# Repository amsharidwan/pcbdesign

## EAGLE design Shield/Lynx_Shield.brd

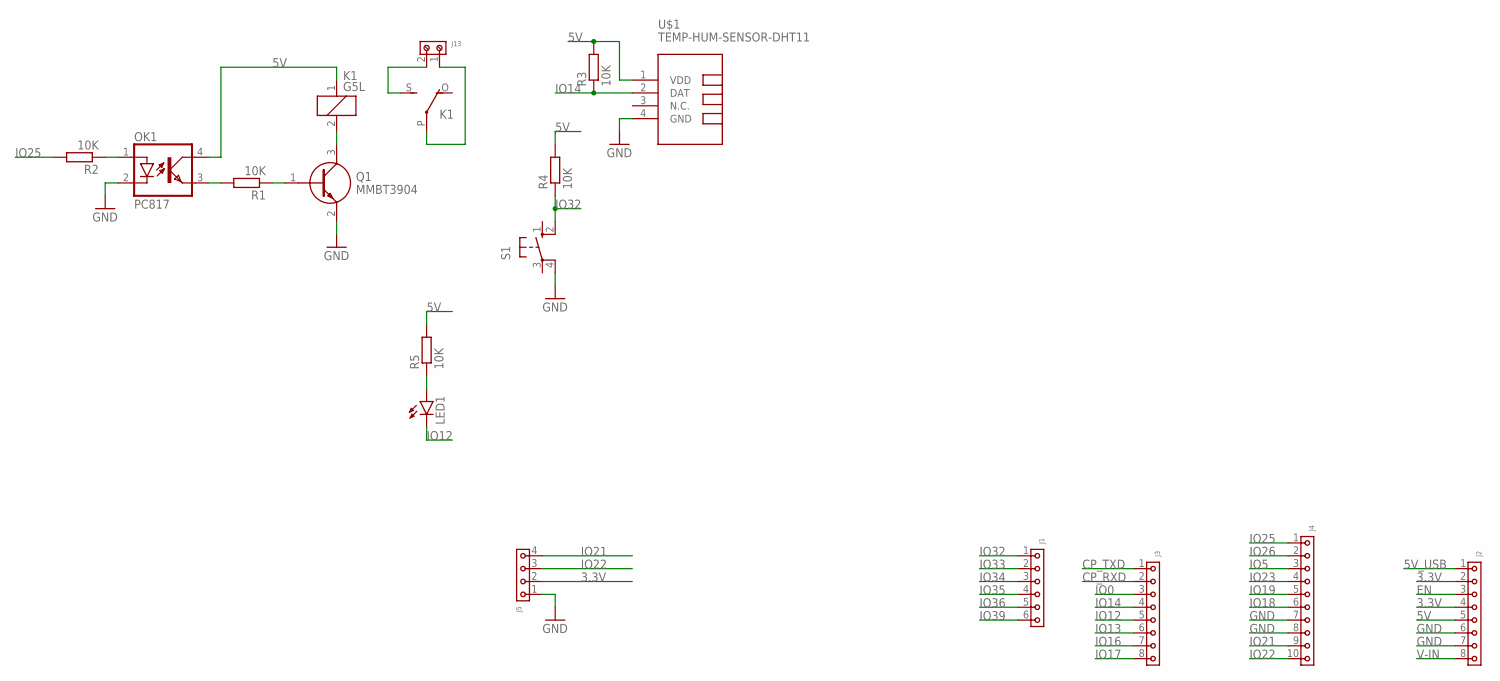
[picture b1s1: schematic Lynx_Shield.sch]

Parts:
J1: 6130XX11821_61300611821; 61300611821
J2, J3: 6130XX11821_61300811821; 61300811821
J4: 6130XX11821_61301011821; 61301011821
J5: 6130XX11821_61300411821; 61300411821
J13: 691134710002
K1: G5L; G5LE
LED1: LED5MM
OK1: PC817; DIL04
Q1: MMBT3904; SOT95P240X120-3N
R1, R2, R3, R4, R5: 10K; R0603
S1: 10-XX; B3F-10XX
U$1: TEMP-HUM-SENSOR-DHT11

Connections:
3.3V: J2.2, J2.4, J5.2
5V: J2.5, K1.1, OK1.4 (COL), R3.2, R4.2, R5.2, U$1.1 (VDD)
5V_USB: J2.1
CP_RXD: J3.2
CP_TXD: J3.1
EN: J2.3
GND: J2.6, J2.7, J4.7, J4.8, J5.1, OK1.2 (C), Q1.2 (E), S1.4 (P1), U$1.4 (GND)
IO0: J3.3
IO5: J4.3
IO12: J3.5, LED1.K (C)
IO13: J3.6
IO14: J3.4, R3.1, U$1.2 (DAT)
IO16: J3.7
IO17: J3.8
IO18: J4.6
IO19: J4.5
IO21: J4.9, J5.4
IO22: J4.10, J5.3
IO23: J4.4
IO25: J4.1, R2.2
IO26: J4.2
IO32: J1.1, R4.1, S1.2 (S1)
IO33: J1.2
IO34: J1.3
IO35: J1.4
IO36: J1.5
IO39: J1.6
unnamed: OK1.3 (EMIT), R1.2
unnamed: J13.2, K1.S
unnamed: J13.1, K1.P
unnamed: OK1.1 (A), R2.1
unnamed: K1.2, Q1.3 (C)
unnamed: Q1.1 (B), R1.1
unnamed: LED1.A, R5.1
V-IN: J2.8

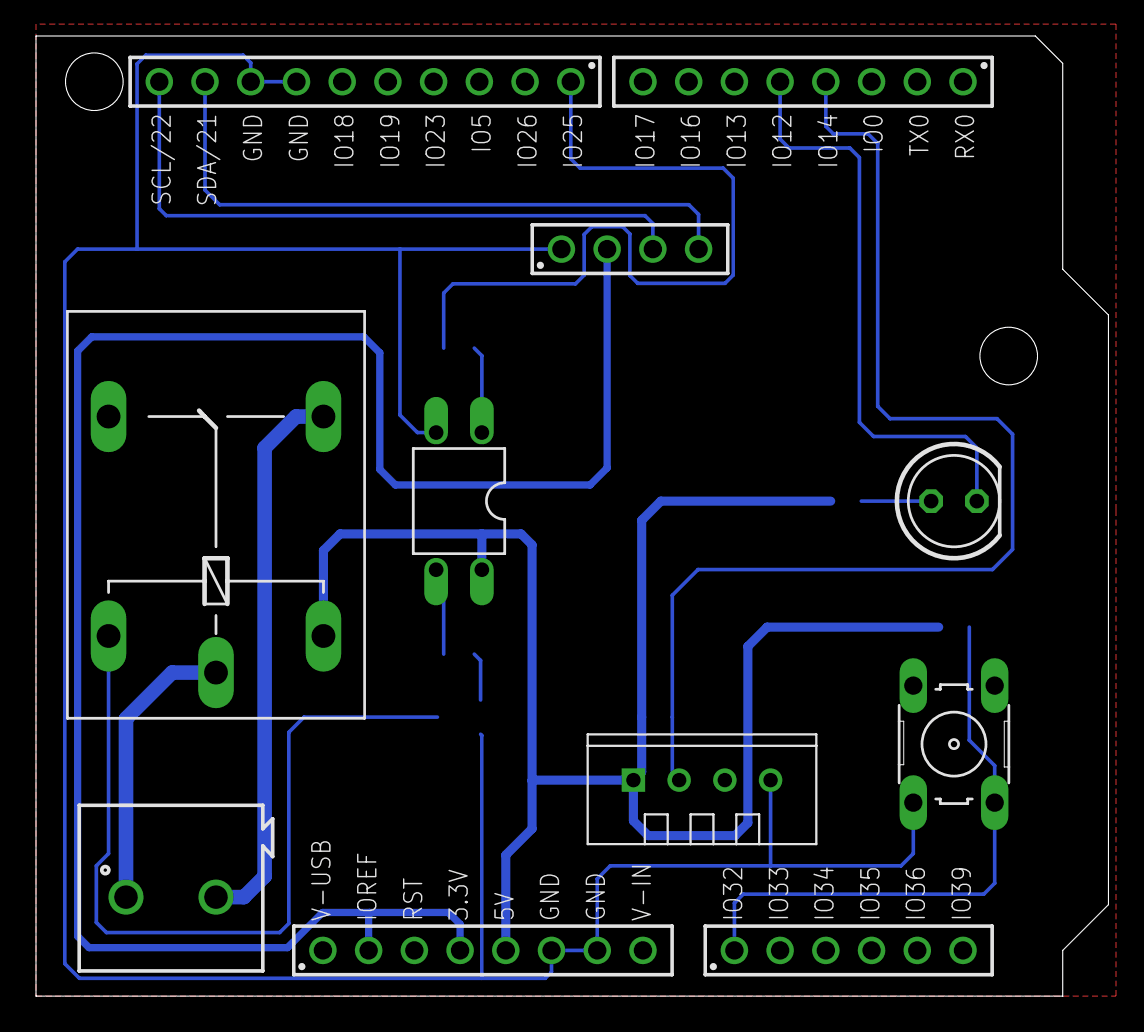
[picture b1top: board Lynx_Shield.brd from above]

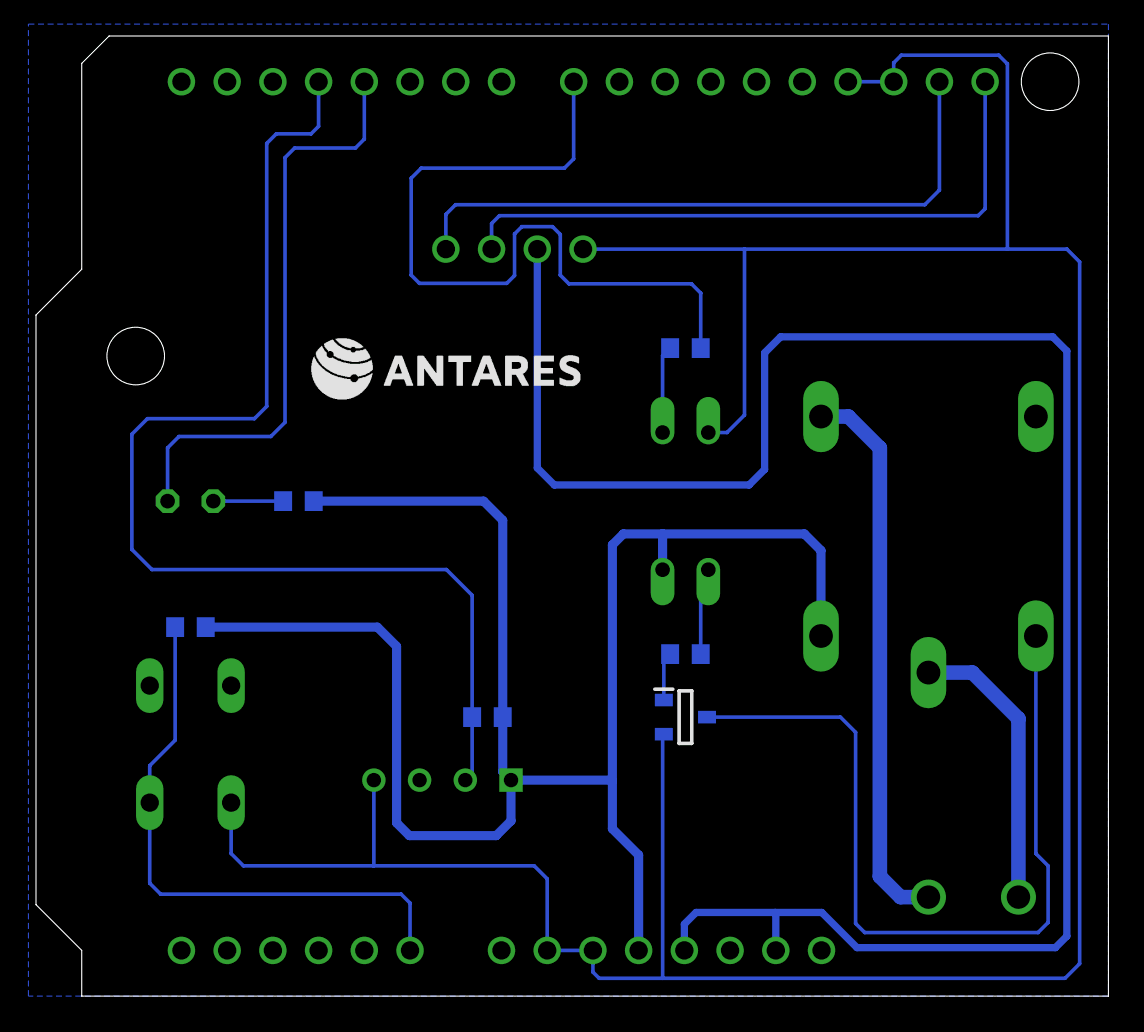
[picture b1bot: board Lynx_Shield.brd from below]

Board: 2 copper layers, 59.6 x 53.3 mm, 17 parts (6 on the bottom side), 16 nets.

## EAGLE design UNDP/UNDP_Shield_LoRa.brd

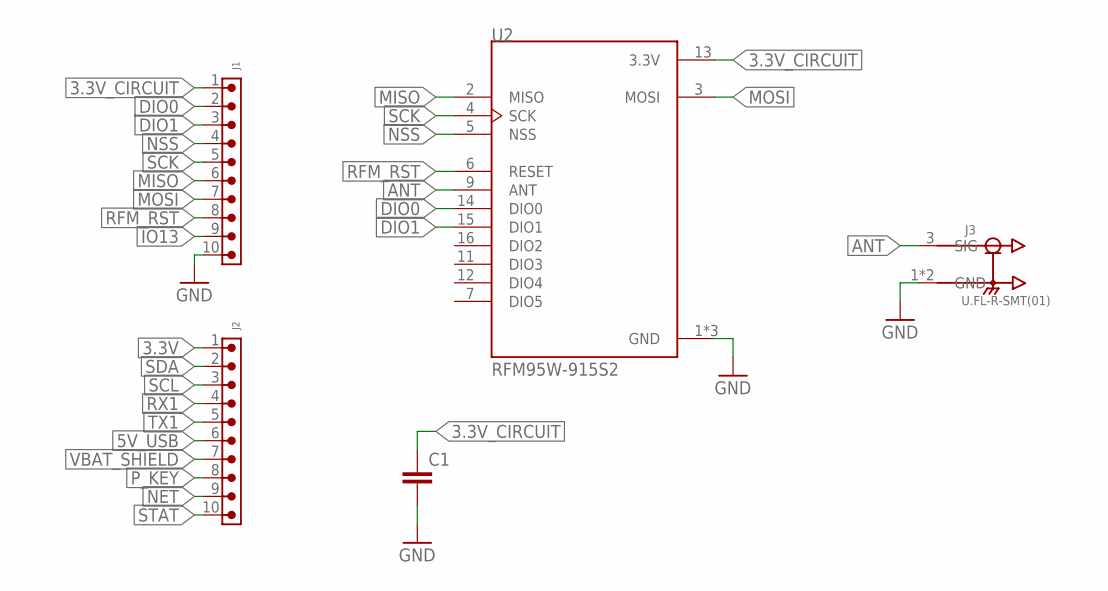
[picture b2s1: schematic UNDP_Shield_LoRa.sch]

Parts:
C1: C-EUC0603; C0603
J1, J2: 6200XX11121_62001011121; 62001011121
J3: U.FL-R-SMT(01); HRS_U.FL-R-SMT(01)
U2: RFM95W-915S2; XCVR_RFM95W-915S2

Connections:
3.3V: J2.1
3.3V_CIRCUIT: C1.1, J1.1, U2.13 (3.3V)
5V_USB: J2.6
ANT: J3.3 (SIG), U2.9 (ANT)
DIO0: J1.2, U2.14 (DIO0)
DIO1: J1.3, U2.15 (DIO1)
GND: C1.2, J1.10, J3.1 (GND), J3.2 (GND), U2.1 (GND), U2.8 (GND), U2.10 (GND)
IO13: J1.9
MISO: J1.6, U2.2 (MISO)
MOSI: J1.7, U2.3 (MOSI)
NET: J2.9
NSS: J1.4, U2.5 (NSS)
P_KEY: J2.8
RFM_RST: J1.8, U2.6 (RESET)
RX1: J2.4
SCK: J1.5, U2.4 (SCK)
SCL: J2.3
SDA: J2.2
STAT: J2.10
TX1: J2.5
VBAT_SHIELD: J2.7

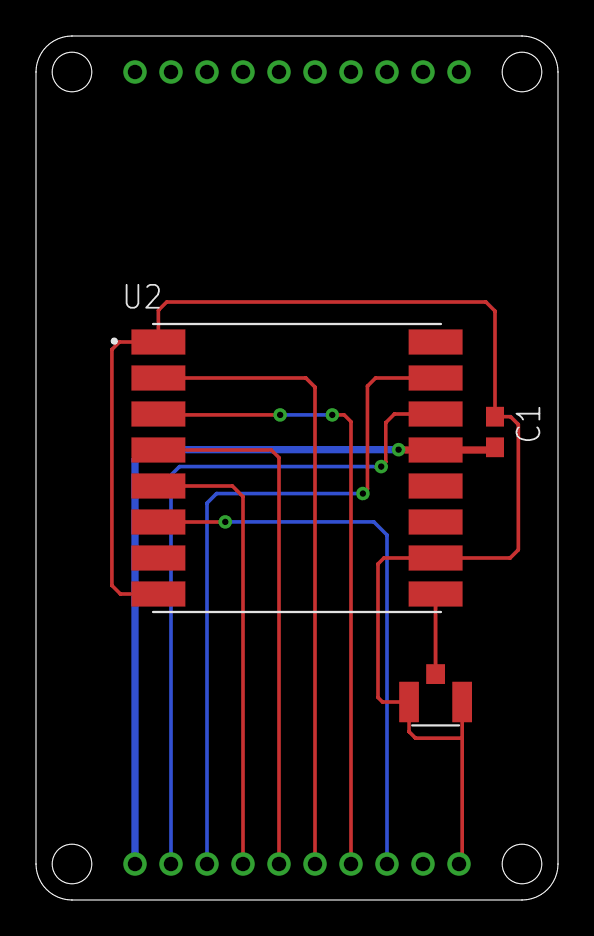
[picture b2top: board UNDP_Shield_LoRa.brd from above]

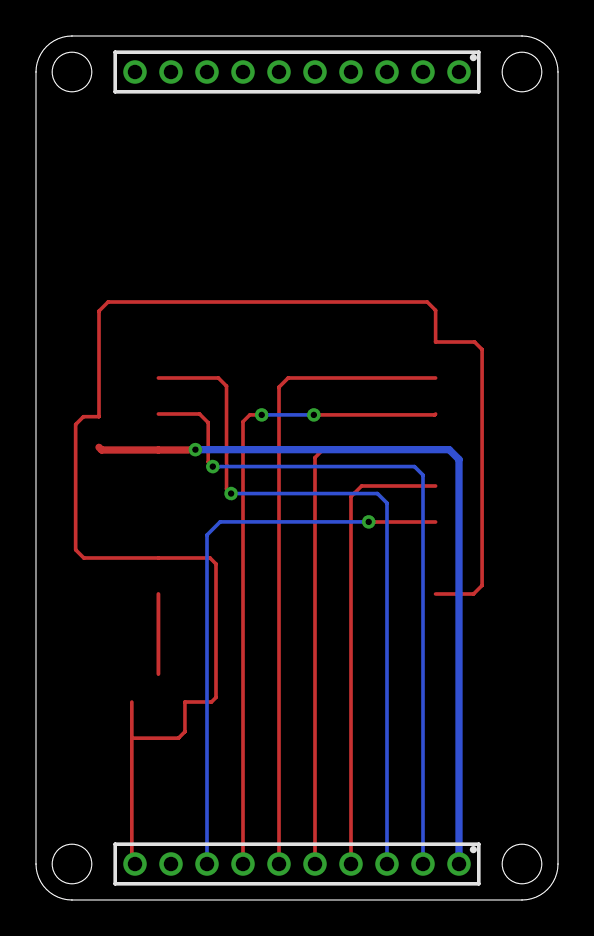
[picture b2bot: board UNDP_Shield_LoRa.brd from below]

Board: 2 copper layers, 29.0 x 48.0 mm, 5 parts (2 on the bottom side), 10 nets.

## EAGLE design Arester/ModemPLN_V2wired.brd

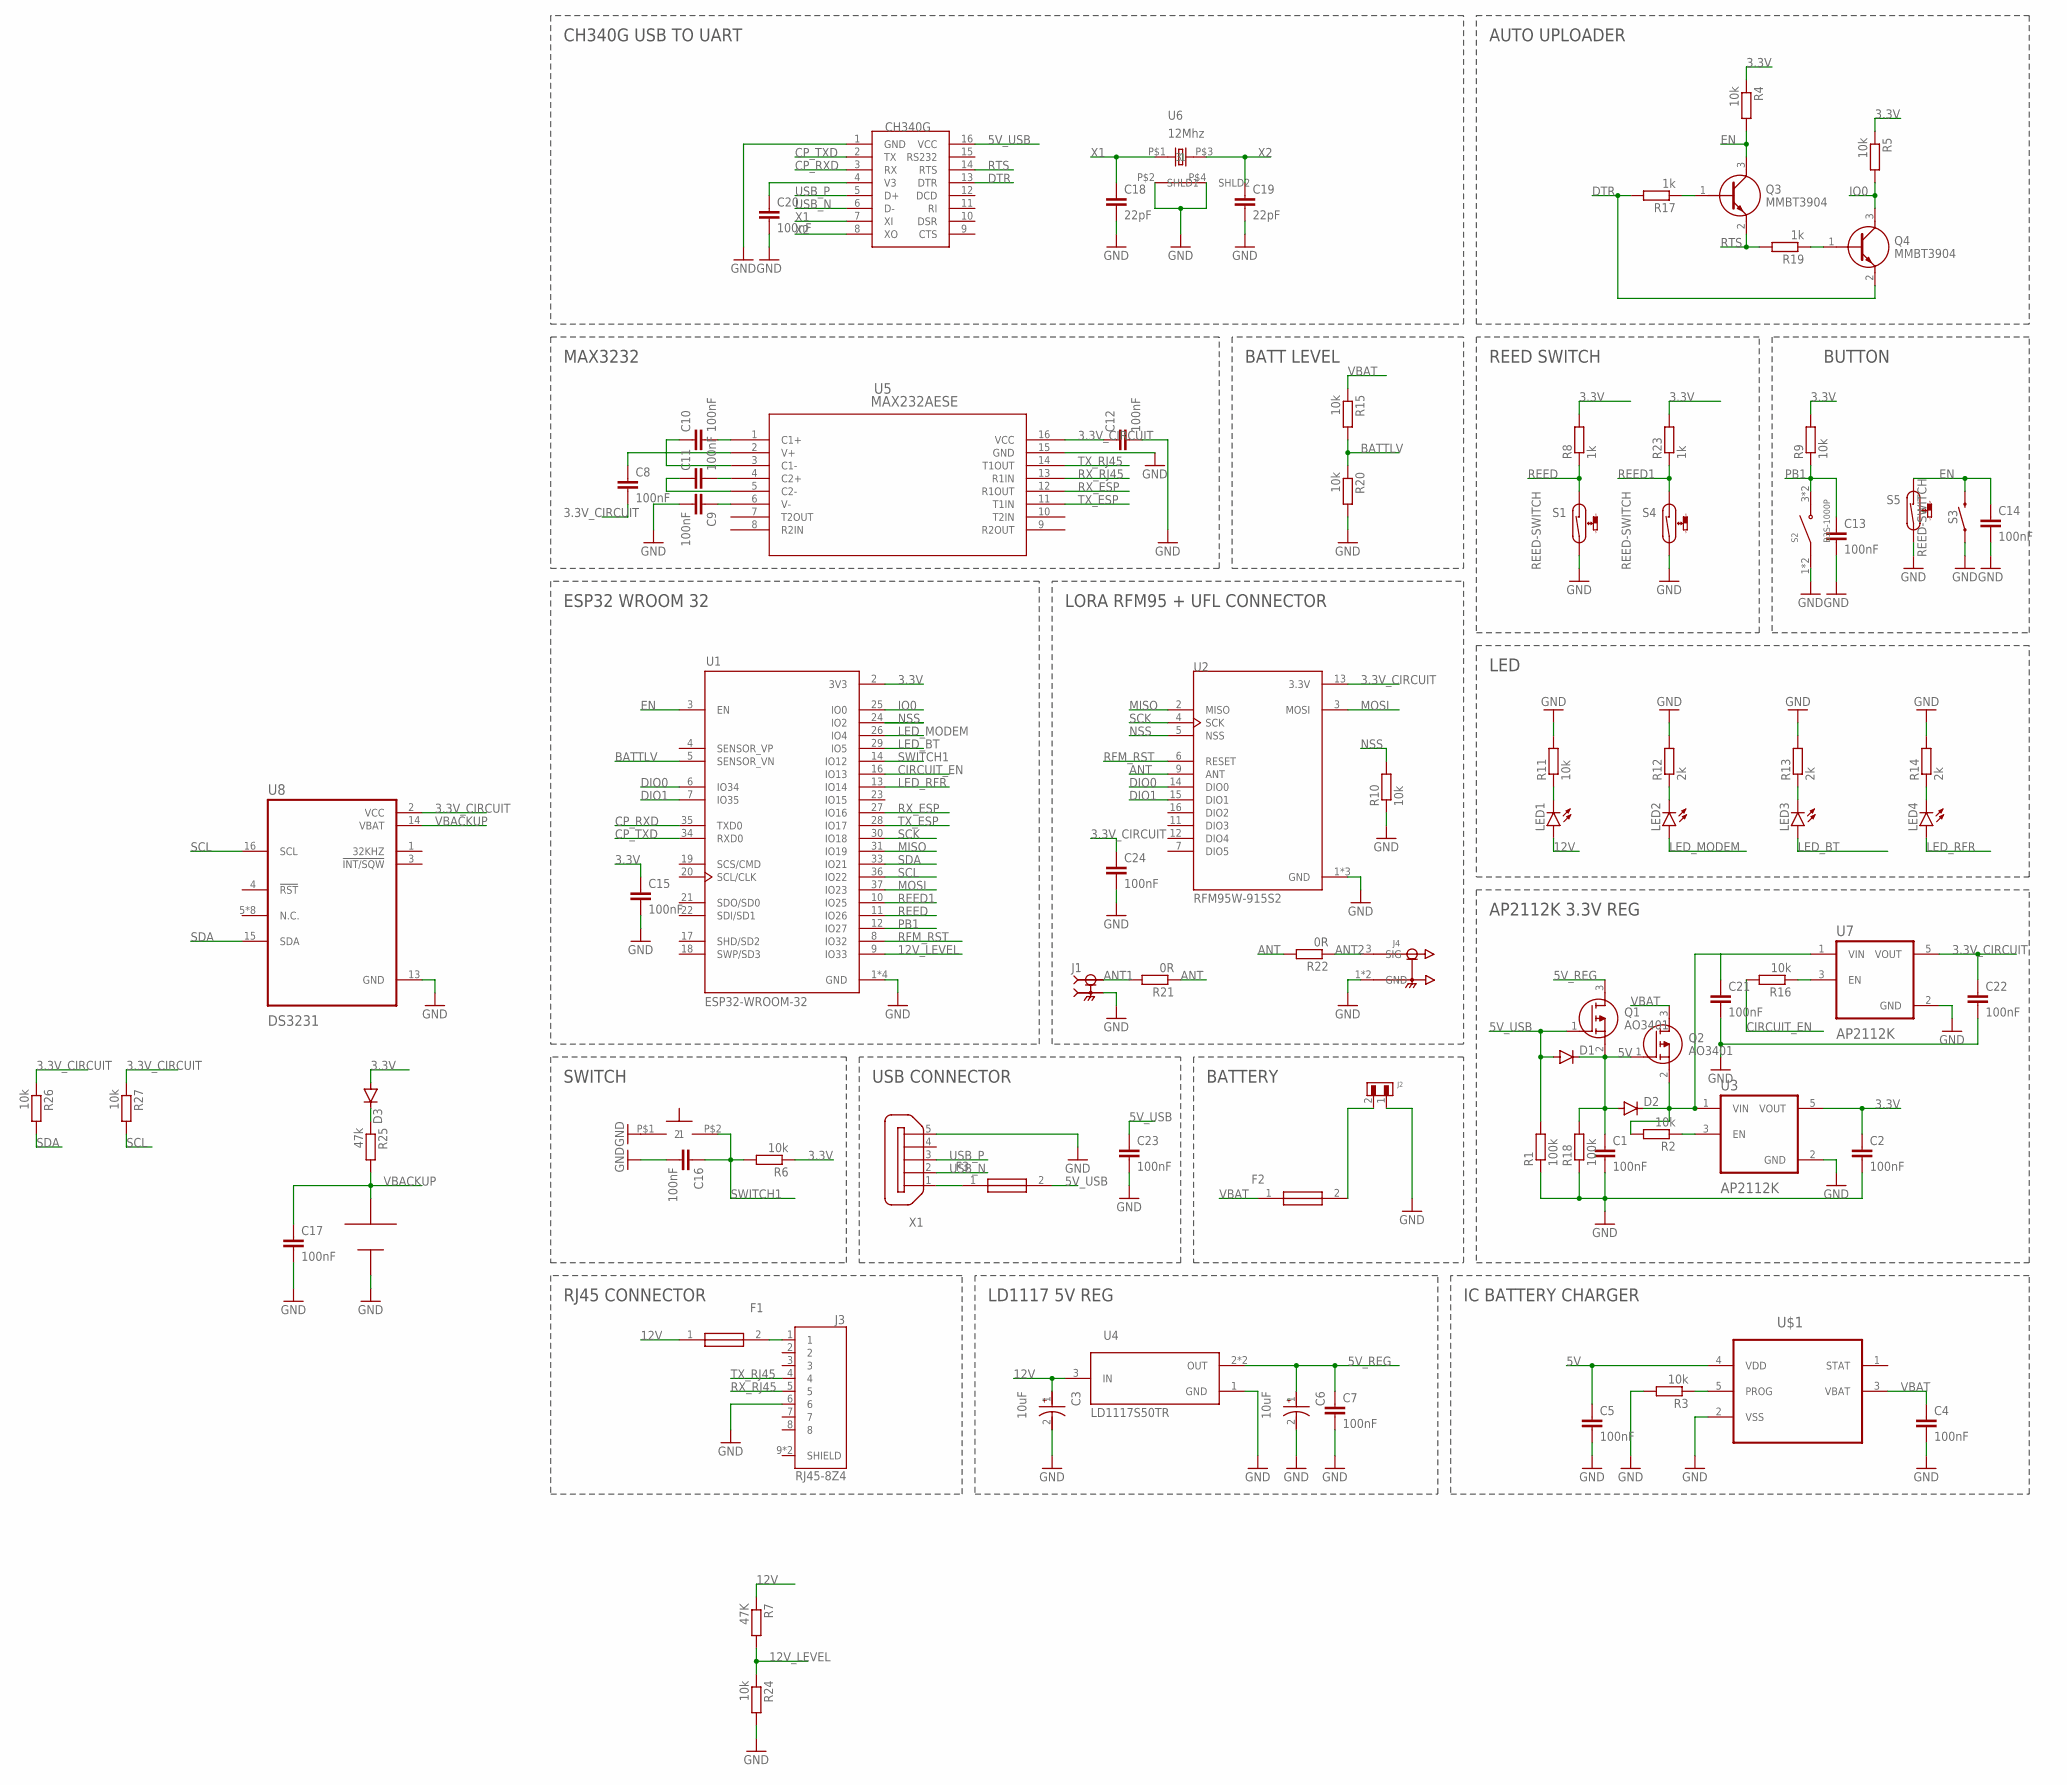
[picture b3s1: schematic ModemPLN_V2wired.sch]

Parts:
C1, C2, C4, C5, C7, C8, C9, C10, C11, C12, C13, C14, C15, C16, C17, C20, C21, C22, C23, C24: 100nF; C0603
C3, C6: 10uF; CAPPM3528X210N
C18, C19: 22pF; C0603
D1, D2, D3: DIODE-DO214AC; DO214AC
F1, F2, F3: MF-NSML260_12-2; FUSC3216X100N
J1: SMA-J-P-X-RA-TH1; SAMTEC_SMA-J-P-X-RA-TH1
J2: 620102131822
J3: RJ45-8Z4; TE_RJ45-8Z4
J4: U.FL-R-SMT(01); HRS_U.FL-R-SMT(01)
LED1, LED2, LED3, LED4: LEDCHIPLED_0805; CHIPLED_0805
Q1, Q2: AO3401; SOT95P280X125-3N
Q3, Q4: MMBT3904; SOT95P240X120-3N
R1, R18: 100k; R0603
R2, R3, R4, R5, R6, R9, R10, R11, R15, R16, R20, R24, R26, R27: 10k; R0603
R7: 47K; R0603
R8, R17, R19, R23: 1k; R0603
R12, R13, R14: 2k; R0603
R21, R22: 0R; R0603
R25: 47k; R0603
S1, S4, S5: REED-SWITCH; MK15
S2: B3S-1000P; SW_B3S-1000P
S3: MOMENTARY-SWITCH-SPST-SMD-6.0X3.5MM; TACTILE_SWITCH_SMD_6.0X3.5MM
U1: ESP32-WROOM-32; MODULE_ESP32-WROOM-32(8MB)
U2: RFM95W-915S2; XCVR_RFM95W-915S2
U3, U7: AP2112K; SOT95P285X140-5N
U4: LD1117S50TR; SOT230P700X180-4N
U5: MAX232AESE; 21-0041B_16
U6: 12Mhz; NX32256A
U8: DS3231; SOIC127P1032X265-16N
U$1: MCP73831T-5ACI/OT; SOT95P280X145-5N
U$2: TACTSWITCH; TACT
U$3: MS621FE
U$4: CH340G; SOIC127P600X175-16N
X1: ZX62D-B-5PA8

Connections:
3.3V: C2.1, C15.1, D3.A, R4.1, R5.1, R6.1, R8.2, R9.2, R23.2, U1.2 (3V3), U3.5 (VOUT)
3.3V_CIRCUIT: C8.2, C12.1, C22.1, C24.1, R26.1, R27.1, U2.13 (3.3V), U5.16 (VCC), U7.5 (VOUT), U8.2 (VCC)
5V: C1.1, C5.1, D1.C, D2.A, Q1.2 (S), Q2.1 (G), R18.2, U$1.4 (VDD)
5V_REG: C6.1, C7.1, Q1.3 (D), U4.2 (OUT), U4.4 (OUT)
5V_USB: C23.1, D1.A, F3.2, Q1.1 (G), R1.2, U$4.16 (VCC)
12V: C3.1, F1.1, LED1.A, R7.1, U4.3 (IN)
12V_LEVEL: R7.2, R24.1, U1.9 (IO33)
ANT: R21.1, R22.2, U2.9 (ANT)
ANT1: J1.1, R21.2
ANT2: J4.3 (SIG), R22.1
BATTLV: R15.2, R20.1, U1.5 (SENSOR_VN)
CIRCUIT_EN: R16.2, U1.16 (IO13)
CP_RXD: U1.35 (TXD0), U$4.3 (RX)
CP_TXD: U1.34 (RXD0), U$4.2 (TX)
DIO0: U1.6 (IO34), U2.14 (DIO0)
DIO1: U1.7 (IO35), U2.15 (DIO1)
DTR: Q4.2 (E), R17.2, U$4.13 (DTR)
EN: C14.1, Q3.3 (C), R4.2, S3.2, S5.1, U1.3 (EN)
GND: C1.2, C2.2, C3.2, C4.2, C5.2, C6.2, C7.2, C9.2, C12.2, C13.2, C14.2, C15.2, C16.2, C17.2, C18.2, C19.2, C20.2, C21.2, C22.2, C23.2, C24.2, J1.2, J1.3 (2), J1.4 (2), J1.5 (2), J2.1, J3.6, J4.1 (GND), J4.2 (GND), R1.1, R3.2, R10.1, R11.2, R12.2, R13.2, R14.2, R18.1, R20.2, R24.2, S1.2, S2.1 (COM), S2.2 (COM), S3.1, S4.2, S5.2, U1.1 (GND), U1.15 (GND), U1.38 (GND), U1.39 (GND), U2.1 (GND), U2.8 (GND), U2.10 (GND), U3.2 (GND), U4.1 (GND), U5.15 (GND), U6.P$2 (SHLD1), U6.P$4 (SHLD2), U7.2 (GND), U8.13 (GND), U$1.2 (VSS), U$2.P$1 (1), U$3.V-, U$4.1 (GND), X1.5
IO0: Q4.3 (C), R5.2, U1.25 (IO0)
LED_BT: LED3.A, U1.29 (IO5)
LED_MODEM: LED2.A, U1.26 (IO4)
LED_RFR: LED4.A, U1.13 (IO14)
MISO: U1.31 (IO19), U2.2 (MISO)
MOSI: U1.37 (IO23), U2.3 (MOSI)
unnamed: LED1.C, R11.1
unnamed: F1.2, J3.1
unnamed: R16.1, U7.3 (EN)
unnamed: R2.1, U3.3 (EN)
unnamed: R3.1, U$1.5 (PROG)
unnamed: C9.1, U5.6 (V-)
unnamed: LED2.C, R12.1
unnamed: C11.2, U5.4 (C2+)
unnamed: C11.1, U5.5 (C2-)
unnamed: C10.2, U5.1 (C1+)
unnamed: C10.1, U5.3 (C1-)
unnamed: LED3.C, R13.1
unnamed: LED4.C, R14.1
unnamed: C21.1, D2.C, Q2.2 (S), R2.2, U3.1 (VIN), U7.1 (VIN)
unnamed: C20.1, U$4.4 (V3)
unnamed: C8.1, U5.2 (V+)
unnamed: F3.1, X1.1
unnamed: D3.C, R25.1
unnamed: Q3.1 (B), R17.1
unnamed: Q4.1 (B), R19.1
unnamed: F2.2, J2.2
NSS: R10.2, U1.24 (IO2), U2.5 (NSS)
PB1: C13.1, R9.1, S2.3 (NO), S2.4 (NO), U1.12 (IO27)
REED: R8.1, S1.1, U1.11 (IO26)
REED1: R23.1, S4.1, U1.10 (IO25)
RFM_RST: U1.8 (IO32), U2.6 (RESET)
RTS: Q3.2 (E), R19.2, U$4.14 (RTS)
RX_ESP: U1.27 (IO16), U5.12 (R1OUT)
RX_RJ45: J3.5, U5.13 (R1IN)
SCK: U1.30 (IO18), U2.4 (SCK)
SCL: R27.2, U1.36 (IO22), U8.16 (SCL)
SDA: R26.2, U1.33 (IO21), U8.15 (SDA)
SWITCH1: C16.1, R6.2, U1.14 (IO12), U$2.P$2 (2)
TX_ESP: U1.28 (IO17), U5.11 (T1IN)
TX_RJ45: J3.4, U5.14 (T1OUT)
USB_N: U$4.6 (D-), X1.2
USB_P: U$4.5 (D+), X1.3
VBACKUP: C17.1, R25.2, U8.14 (VBAT), U$3.V+
VBAT: C4.1, F2.1, Q2.3 (D), R15.1, U$1.3 (VBAT)
X1: C18.1, U6.P$1 (1), U$4.7 (XI)
X2: C19.1, U6.P$3 (3), U$4.8 (XO)

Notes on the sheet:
SWITCH
RJ45 CONNECTOR
LD1117 5V REG
IC BATTERY CHARGER
BATTERY
AP2112K 3.3V REG
LED
LORA RFM95 + UFL CONNECTOR
ESP32 WROOM 32
MAX3232
BATT LEVEL
REED SWITCH
BUTTON
USB CONNECTOR
CH340G USB TO UART
AUTO UPLOADER

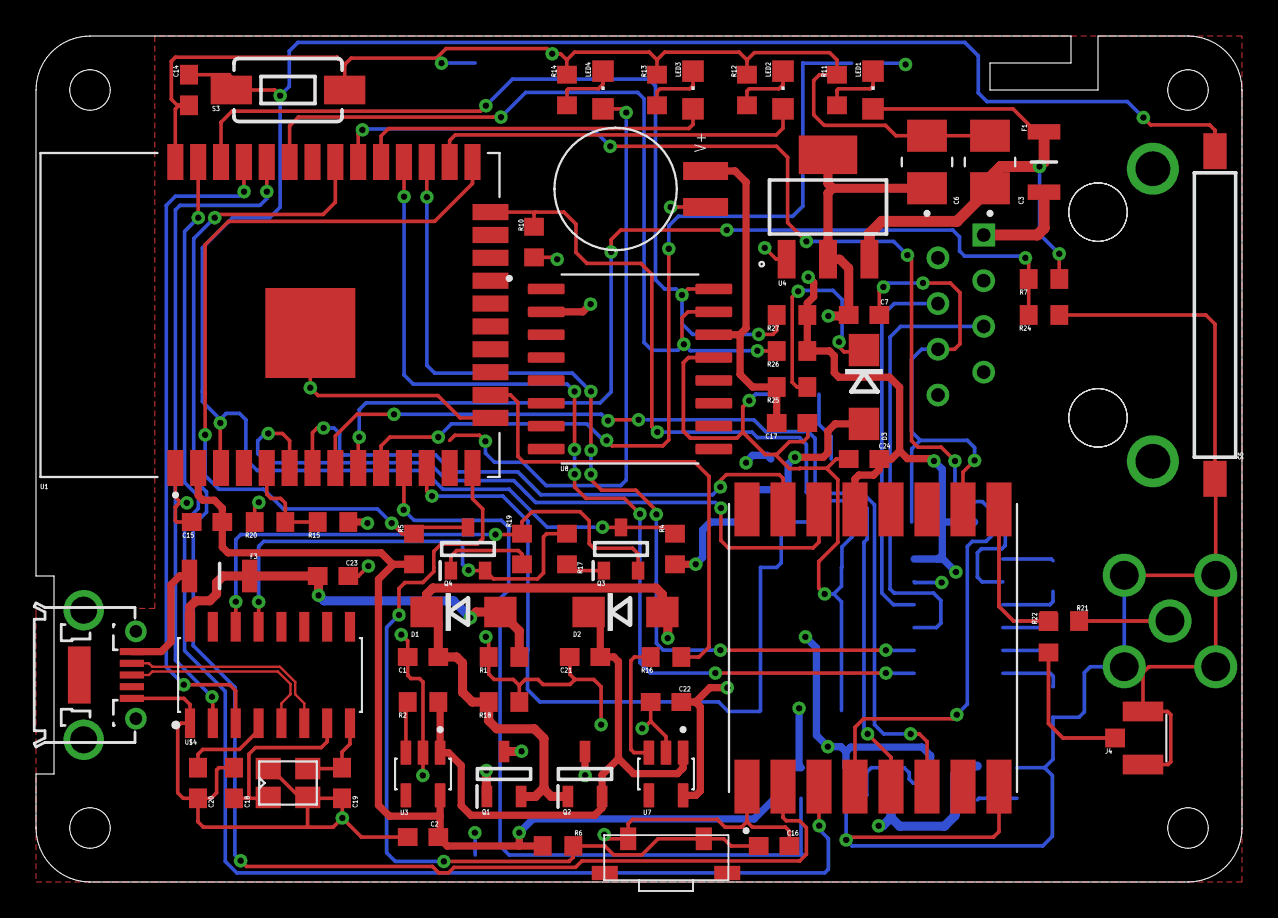
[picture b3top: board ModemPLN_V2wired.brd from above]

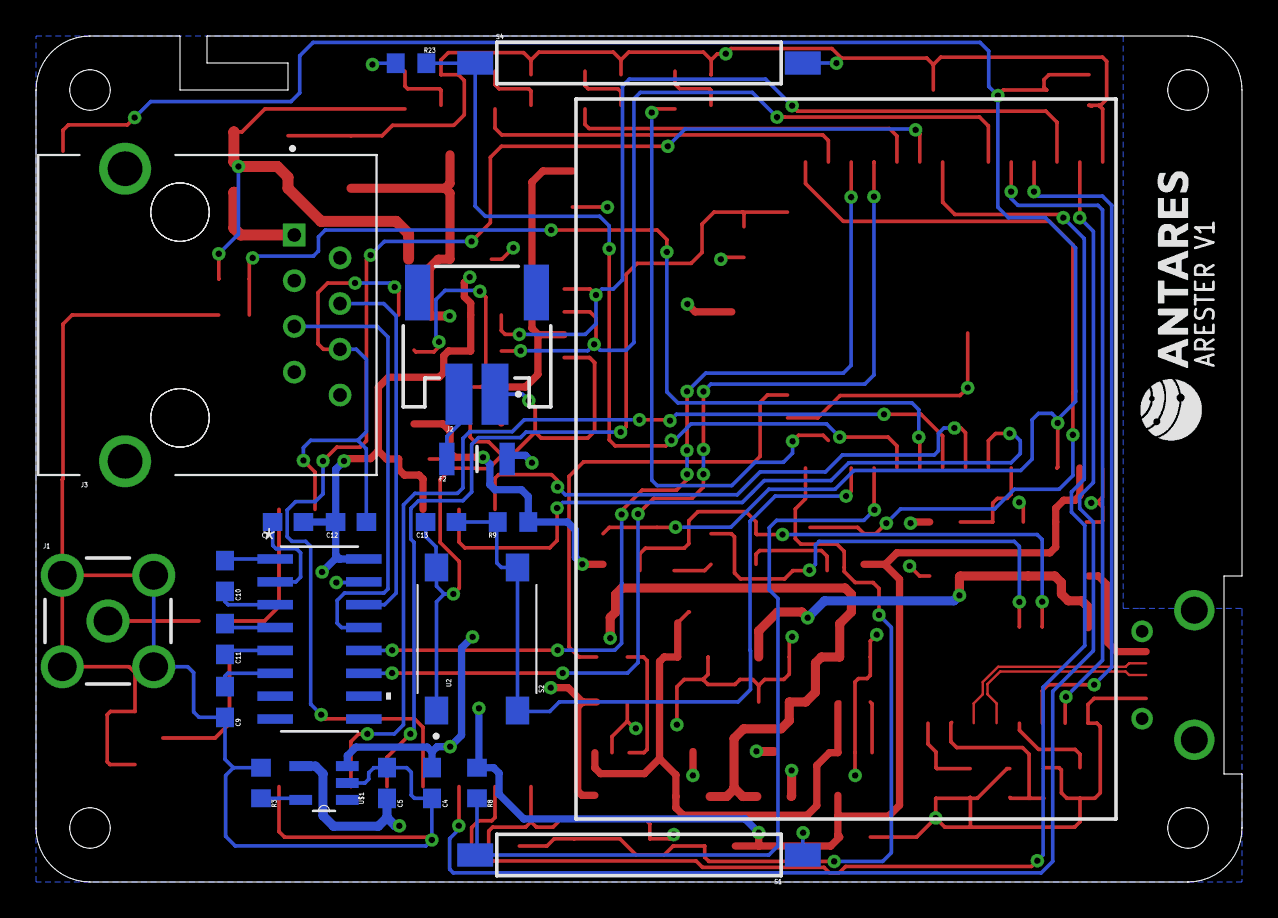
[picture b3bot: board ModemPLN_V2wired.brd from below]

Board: 4 copper layers, 67.0 x 47.0 mm, 87 parts (21 on the bottom side), 66 nets.

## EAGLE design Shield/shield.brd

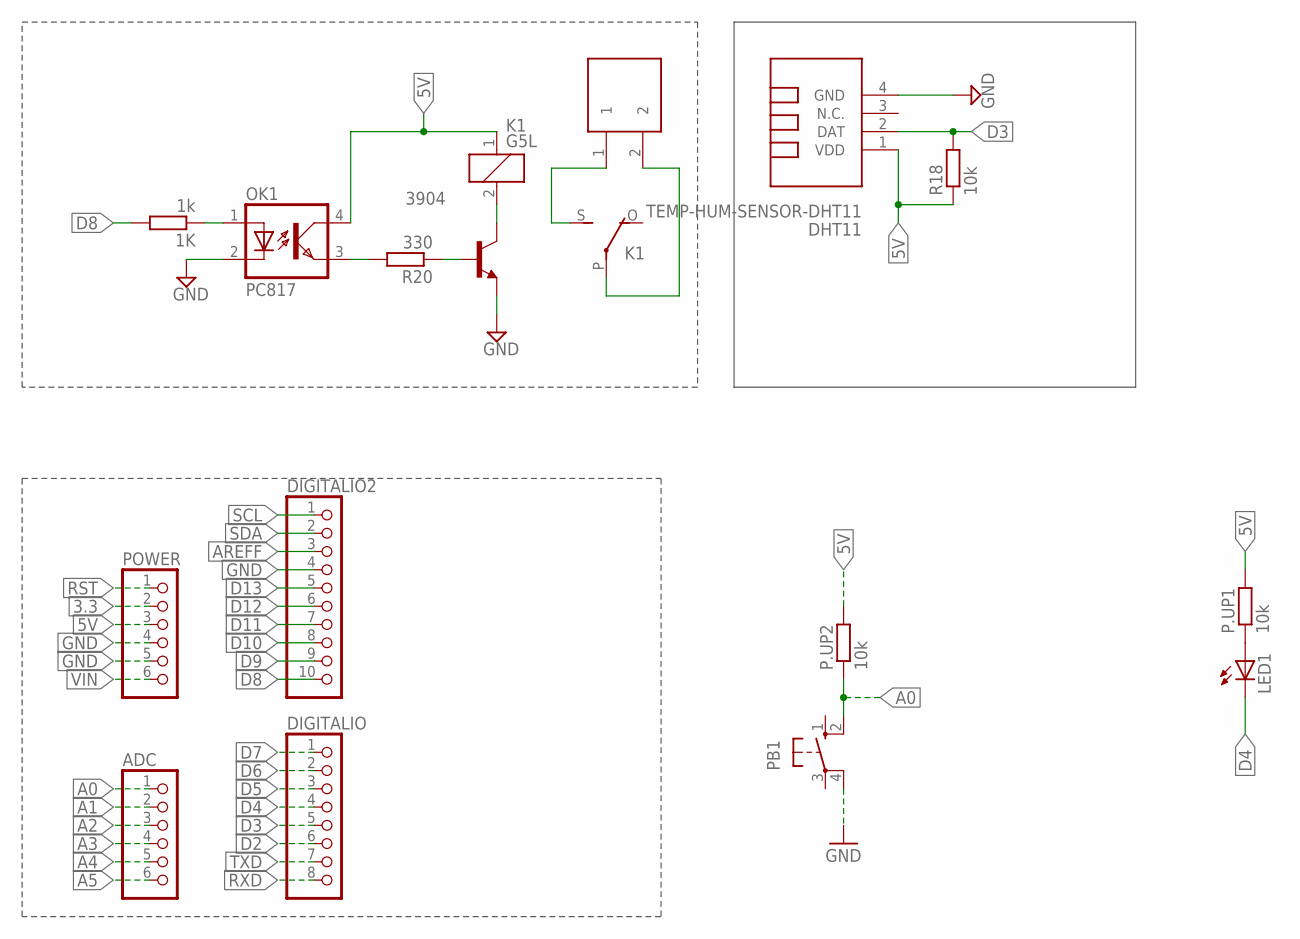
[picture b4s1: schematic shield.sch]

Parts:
1K: 1k; R0805
3904: MMBT3904LT1-NPN-SOT23-BEC; SOT23-BEC
ADC: PINHD-1X6; 1X06
DHT11: TEMP-HUM-SENSOR-DHT11
DIGITALIO: PINHD-1X8; 1X08
DIGITALIO2: PINHD-1X10; 1X10
K1: G5L; G5LE
LED1: LED5MM
OK1: PC817; DIL04
P.UP1, P.UP2: 10k; R0805
PB1: 10-XX; B3F-10XX
POWER: PINHD-1X6; 1X06
R18: 10k; R0805
R20: 330; R0805
U$8: TBLOCK2PIN; 2PIN

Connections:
3.3: POWER.2
5V: DHT11.1 (VDD), K1.1, OK1.4 (COL), P.UP1.2, P.UP2.2, POWER.3, R18.1
A0: ADC.1, P.UP2.1, PB1.2 (S1)
A1: ADC.2
A2: ADC.3
A3: ADC.4
A4: ADC.5
A5: ADC.6
AREFF: DIGITALIO2.3
D2: DIGITALIO.6
D3: DHT11.2 (DAT), DIGITALIO.5, R18.2
D4: DIGITALIO.4, LED1.K (C)
D5: DIGITALIO.3
D6: DIGITALIO.2
D7: DIGITALIO.1
D8: 1K.2, DIGITALIO2.10
D9: DIGITALIO2.9
D10: DIGITALIO2.8
D11: DIGITALIO2.7
D12: DIGITALIO2.6
D13: DIGITALIO2.5
GND: 3904.E, DHT11.4 (GND), DIGITALIO2.4, OK1.2 (C), PB1.4 (P1), POWER.4, POWER.5
LOAD: K1.P, U$8.2
unnamed: K1.S, U$8.1
unnamed: LED1.A, P.UP1.1
unnamed: 1K.1, OK1.1 (A)
unnamed: OK1.3 (EMIT), R20.2
unnamed: 3904.B, R20.1
unnamed: 3904.C, K1.2
RST: POWER.1
RXD: DIGITALIO.8
SCL: DIGITALIO2.1
SDA: DIGITALIO2.2
TXD: DIGITALIO.7
VIN: POWER.6

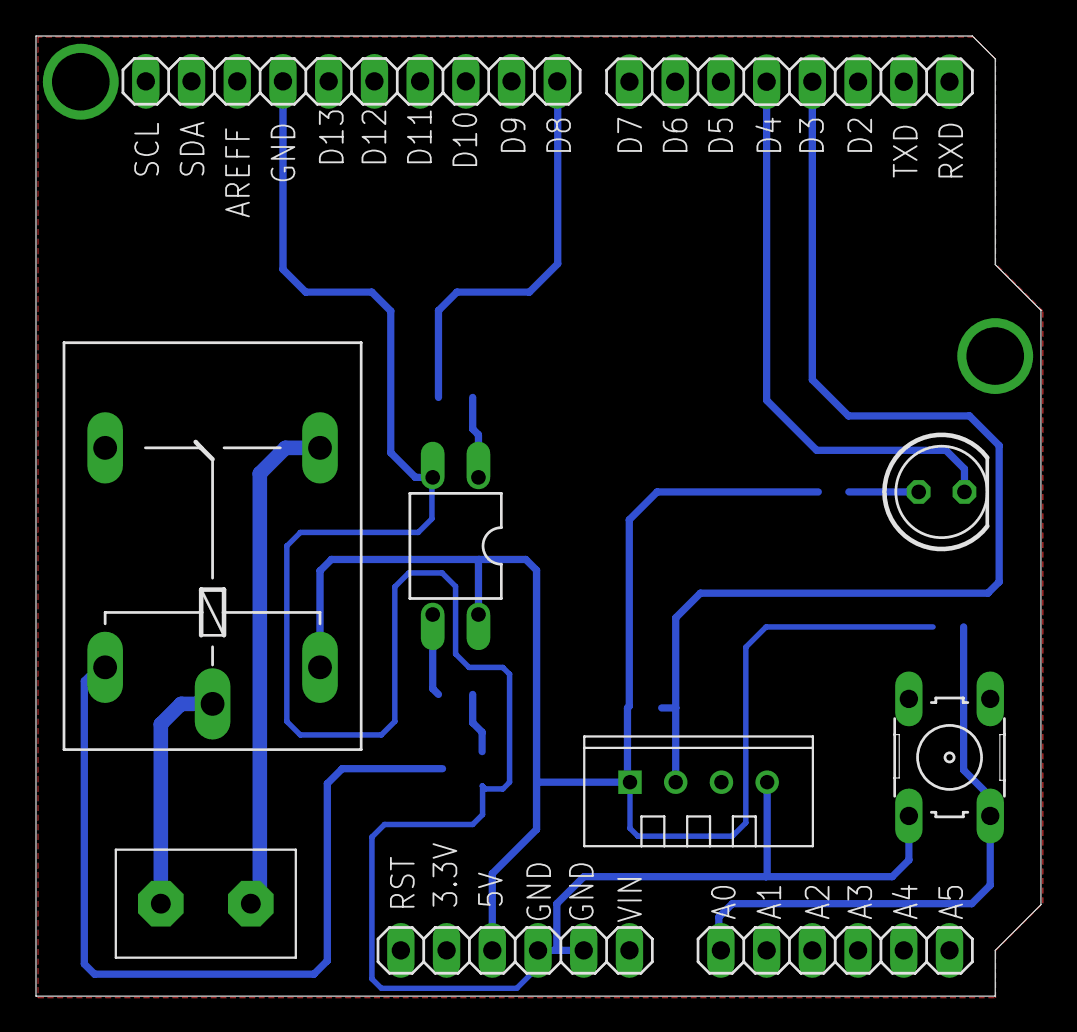
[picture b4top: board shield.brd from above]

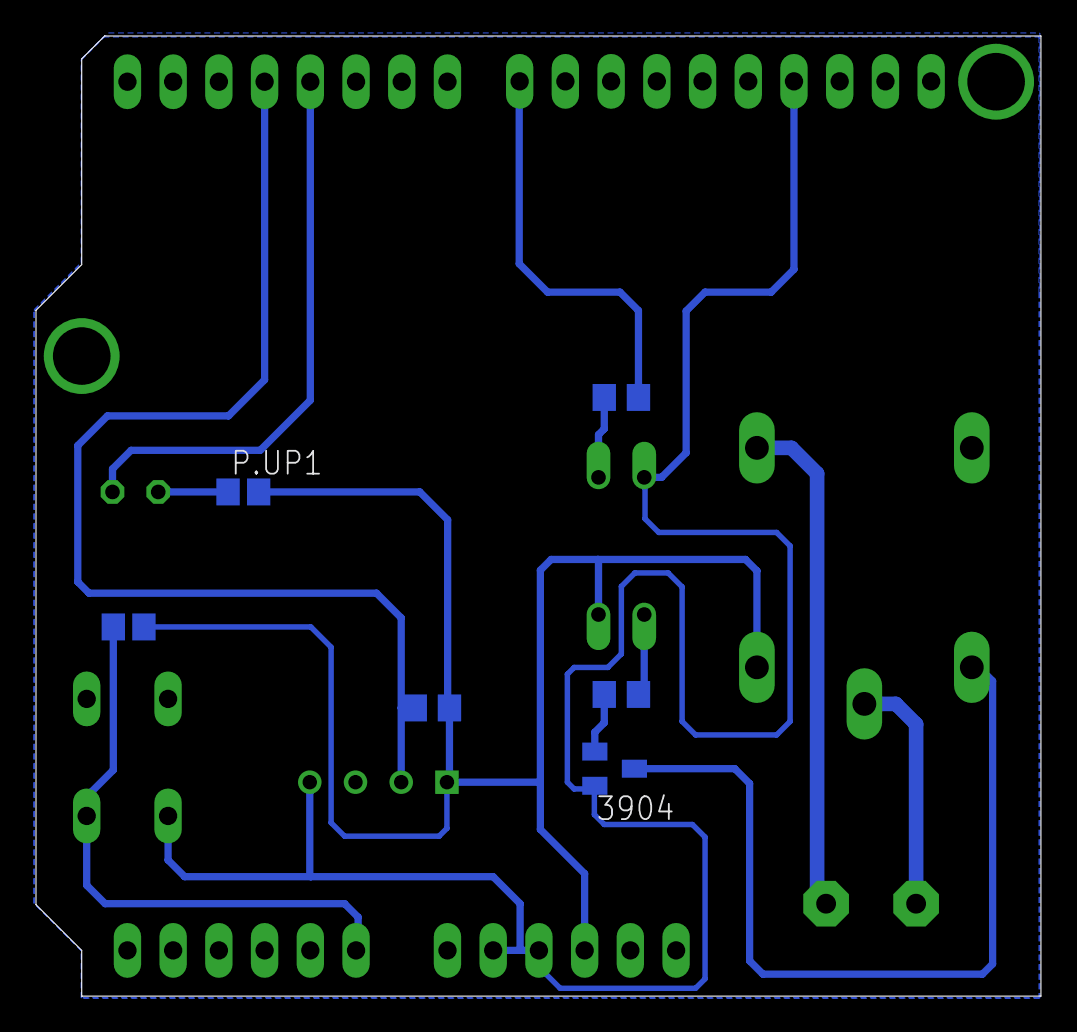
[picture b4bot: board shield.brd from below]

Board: 2 copper layers, 55.8 x 53.3 mm, 16 parts (6 on the bottom side), 13 nets.

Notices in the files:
parts and their libraries:
SparkFun-Switches: Licensing: Creative Commons ShareAlike 4.0 International - https://creativecommons.org/licenses/by-sa/4.0
Wurth_Connectors_WR-WTB: Copyright: Würth Elektronik
